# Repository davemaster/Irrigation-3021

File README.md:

# Irrigation-3021
(https://blogs.embarcadero.com/building-good-with-cbuilder-contest-results/)

https://blogs.embarcadero.com/building-good-with-cbuilder-contest-results/ 
https://youtube.com/embed/tNYx-wSfjVc

How Bluetooth Technology can improve the use of water resources worldwide. Programming using [C++ Builder 10.3 Community Edition](https://www.embarcadero.com/es/products/cbuilder/starter) was surprisly very faster than the turtle of Android Studio and its eternal indexing-nightmares; So, its time to move forward using this IDE, in this project, using the multi-device features. 

The goal, more control over the water use in irrigation issues, first in my mom's garden, then in the city parks, then Farmlands, then in any water distribution activity worldwide. Thanks to the [Building Good with C++Builder Contest](https://blogs.embarcadero.com/building-good-with-cbuilder-contest/) for giving this oportunity.

# Project Resume
The system is going to use a bluetooth capable device to control a valve to irrigate a plant. The control-device can be a laptop/pc or a smartphone (Android or iOS). These devices control through bluetooth wireless link an Arduino UNO board connected to a HC-05 bluetooth module; so this last can open/close the solenoid valve by a relay; according the following modes: 1. Based on sensors (humidity, water tank level, and rain intensitivity) the Arduino will decide when to open/close the valve to properly water the plant. The sensors values will be compared with setpoints to make decisions. Mode 2. Test mode, we can open/close valve no matter the sensors values. Mode 3, using irrigation schedules, ie, time defined periods when the valve will be open.

# Needed Parts
1. Mobile Phone: Iphone, Android or laptop/pc Bluetooth capable. C++ Builder 10.3 can program them all with ONE project at the same time; pretty GOOD!!!.

2. Arduino Board: UNO, NANO, MEGA, etc. https://www.arduino.cc/en/Main/Products

3. HC-05 Bluetooth Module https://www.siarperu.com/store/#view=00011&busq=hc-05

4. A 12V solenoid Valve https://www.sparkfun.com/products/10456

5. Some Protoboards cabling, female-male, male-male or female-female https://naylampmechatronics.com/accesorios-y-prototipado/26-cable-para-protoboard.html

6. Sensors for Humidity moisture, rain intensitivity, and water level:

# Needed Software
1. Embarcadero C++ Builder 10.3 Community Edition https://www.embarcadero.com/products/cbuilder/starter or lastest https://embarcadero.com/products/cbuilder

2. Arduino IDE 1.8.15 https://www.arduino.cc/en/software

3. Any Serial Terminal (for PC Windows or Mac where the C++ Builder is installed)

4. Proteus 8.6 with Arduino libraries for simulate Arduino valve control and the sensors attached (humidity, water leve, and rain) lectures and response of the valve
   control system (circuit and firmware) to commands from Irrigation 3021 app programmed in C++ Builder. 

5. In my particular case, I used the scrcpy for see my project (Irrigation 3021) in its Android versión. https://github.com/Genymobile/scrcpy

SOURCE CODE UPDATED

In file BTReadThread.cpp, the following changes has been made:

.................................

  else if(cmd==2)
		{
			dataFromArduino=Socket->ReceiveData();

			if(dataFromArduino.Length>0)
			{
				StrReceived = TEncoding::ASCII->GetString(dataFromArduino);

				/*************************************/
				AllReceivedData+=StrReceived;

				msg=AllReceivedData;
				Synchronize(TabbedForm->WriteMemo);

				if(AllReceivedData.Length()>12)
				{
					sensors=AllReceivedData;
					Synchronize(TabbedForm->UpdateValueSensors);

					AllReceivedData="";
					Sleep(100);
				}

				#ifndef __ANDROID__
				else
					AllReceivedData="";
				#endif

				/*****************************************/

				/*msg=StrReceived;
				Synchronize(TabbedForm->WriteMemo);

				if(msg.Length()>3)
				{

					sensors=StrReceived;
					Synchronize(TabbedForm->UpdateValueSensors);

				} */
			}

			Sleep(100);
		}

..................................

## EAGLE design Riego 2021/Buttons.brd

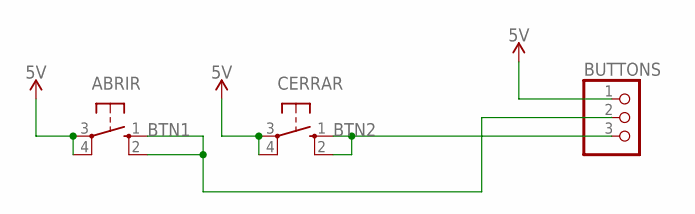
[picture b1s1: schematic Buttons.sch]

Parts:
ABRIR: 10-XX; B3F-10XX
BUTTONS: PINHD-1X3; 1X03
CERRAR: 10-XX; B3F-10XX

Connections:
5V: ABRIR.3, ABRIR.4 (P1), BUTTONS.1, CERRAR.3, CERRAR.4 (P1)
BTN1: ABRIR.1 (S), ABRIR.2 (S1), BUTTONS.2
BTN2: BUTTONS.3, CERRAR.1 (S), CERRAR.2 (S1)

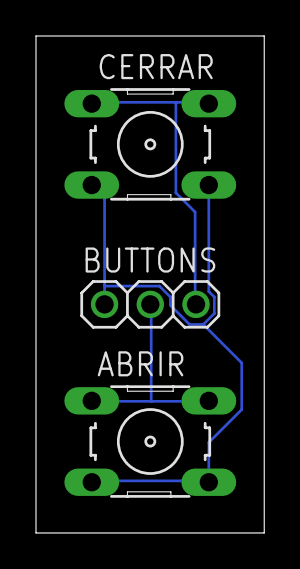
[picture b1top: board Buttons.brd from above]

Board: 2 copper layers, 12.7 x 27.6 mm, 3 parts (0 on the bottom side), 3 nets.

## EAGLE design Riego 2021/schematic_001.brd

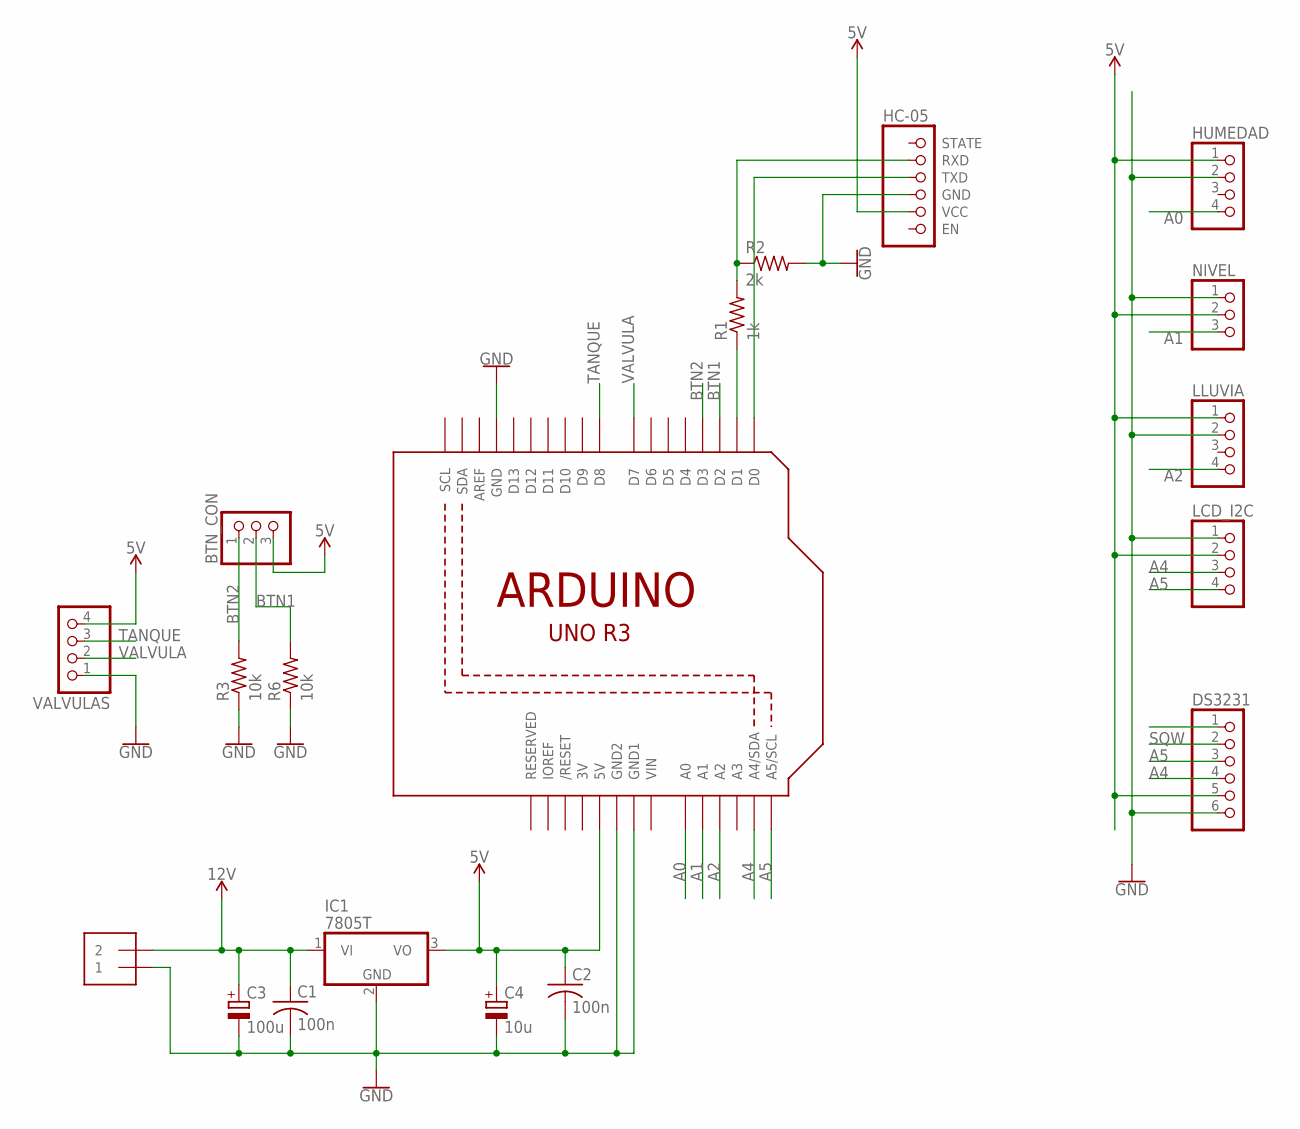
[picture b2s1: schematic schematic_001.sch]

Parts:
BTN_CON: PINHD-1X3; 1X03
C1, C2: 100n; C050-024X044
C3: 100u; E2,5-7
C4: 10u; E2,5-7
DS3231: PINHD-1X6; 1X06
HC-05: HC-05; 1X06
HUMEDAD: PINHD-1X4; 1X04
IC1: 7805T; TO220H
J1: 1X2-3.5MM
LCD_I2C: PINHD-1X4; 1X04
LLUVIA: PINHD-1X4; 1X04
NIVEL: PINHD-1X3; 1X03
R1: 1k; 0204/7
R2: 2k; 0204/7
R3, R6: 10k; 0204/7
U1: ARDUINOR3-BPLACE
VALVULAS: PINHD-1X4; 1X04

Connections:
3V: U1.3V
5V: BTN_CON.3, C2.1, C4.+, DS3231.5, HC-05.5 (VCC), HUMEDAD.1, IC1.3 (VO), LCD_I2C.2, LLUVIA.1, NIVEL.2, U1.5V, VALVULAS.4
12V: C1.1, C3.+, IC1.1 (VI), J1.2
A0: HUMEDAD.4, U1.A0
A1: NIVEL.3, U1.A1
A2: LLUVIA.4, U1.A2
A4: DS3231.4, LCD_I2C.3, U1.A4 (A4/SDA)
A5: DS3231.3, LCD_I2C.4, U1.A5 (A5/SCL)
BTN1: BTN_CON.2, R6.2, U1.D2
BTN2: BTN_CON.1, R3.2, U1.D3
GND: C1.2, C2.2, C3.-, C4.-, DS3231.6, HC-05.4 (GND), HUMEDAD.2, IC1.2 (GND), J1.1, LCD_I2C.1, LLUVIA.2, NIVEL.1, R2.2, R3.1, R6.1, U1.GND, U1.GND1, U1.GND2, VALVULAS.1
unnamed: HC-05.2 (RXD), R1.2, R2.1
unnamed: R1.1, U1.D1
unnamed: HC-05.3 (TXD), U1.D0
SQW: DS3231.2
TANQUE: U1.D8, VALVULAS.3
VALVULA: U1.D7, VALVULAS.2
VIN: U1.VIN

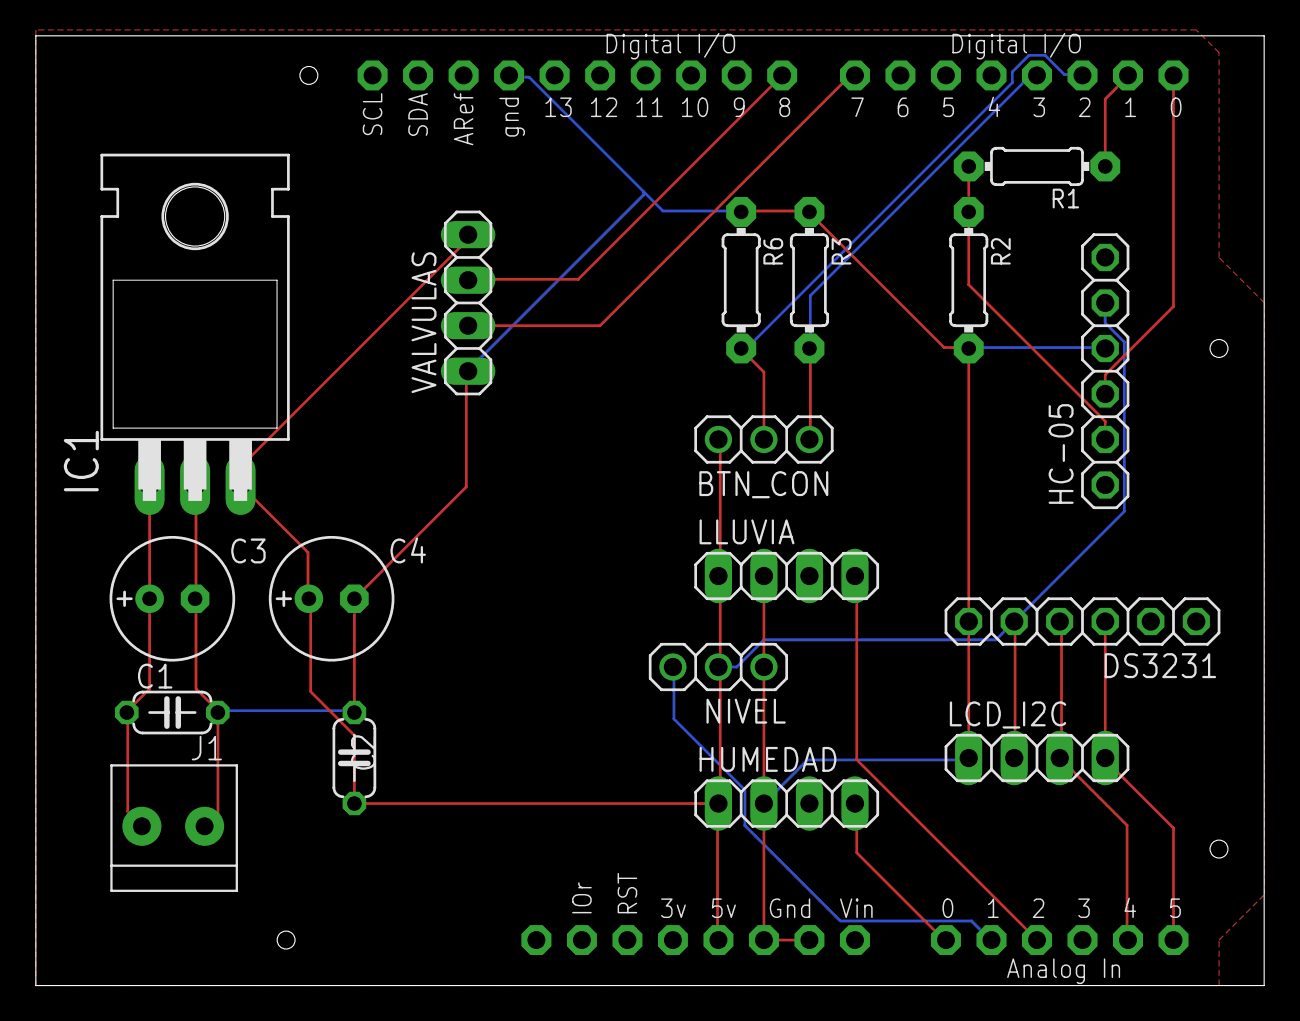
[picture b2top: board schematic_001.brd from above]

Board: 2 copper layers, 68.6 x 53.0 mm, 19 parts (0 on the bottom side), 15 nets.

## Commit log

2021-07-27 /Arduino
2021-07-27 Rename irrigation_3021.inoE to Arduino/irrigation_3021.ino
    sketch tested on Arduino UNO
2021-07-28 Add files via upload
    Eagle PCB Board. Builded by NEXTPCB.
2021-07-28 Create test
2021-07-28 Proteus project simulation files
2021-07-28 Test Videos
    Both, the same test: one from PC, the other from a video recorded by phone
2021-07-28 Irrigation 3021 code for C++ Builder
    Irrigation 3021 code for C++ Builder Community Edition 10.3.3
2021-07-28 video on youtube
    https://www.youtube.com/watch?v=tNYx-wSfjVc
2021-07-30 Changes in BTReadThread.cpp file
    The following changes was made for reading the setpoints of sensors from Valve in both, windows, and Android:
    .................
    else if(cmd==2)
    {
    dataFromArduino=Socket->ReceiveData();
    if(dataFromArduino.Length>0)
2021-07-30 Delete VIDEOS directory
    too big
2021-07-30 Update README.md
    Code updated
2021-08-02 not needed to avoid else part
    This is not needed int C++ Builder Communitity 10.4 version:
    //#ifndef __ANDROID__
    else
    AllReceivedData="";
    //#endif
2021-09-24 Contest Results
    The results

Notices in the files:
parts and their libraries:
SparkFun-PowerSymbols: Licensing: Creative Commons ShareAlike 4.0 International - https://creativecommons.org/licenses/by-sa/4.0
